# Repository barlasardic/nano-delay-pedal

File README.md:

# Arduino Nano Delay Pedal

A compact guitar delay pedal prototype built around a classic Arduino Nano, with a **300 ms delay target**. The schematic and two-layer PCB are complete as a first hardware draft. **Firmware has not been developed, the circuit has not been built or tested, and the enclosure fit is not confirmed.**

## Revision C layout

The **55.88 × 88.90 mm** PCB has rounded corners and four M2.5 mounting holes. It targets a custom compact pedal enclosure. The [mechanical drawing](docs/mechanical-fit.pdf) shows the proposed enclosure arrangement and an exact PCB mounting template; actual hardware clearances still need confirmation.

Input J2 and output J3 are on opposite side edges. The Nano USB socket faces the right side and overhangs the board by about 1.3 mm. Power traces are wider, the regulator bypass capacitors are closer to U1, and the Nano supply and final ADC filter capacitors sit next to their corresponding Nano pins. The circuit connections and component values are unchanged from revision B.

Component values are printed on the front where space permits. The back includes all 57 reference/value labels, connector functions and polarities. See the [two-page assembly guide](docs/assembly-top.pdf) and [review notes](docs/design-review.md).

## Hardware

- **55.88 × 88.90 mm**, two-layer PCB with four M2.5 mounting holes.
- Socketed Arduino Nano and through-hole components.
- **23LC1024-I/P SPI SRAM** for the planned delay buffer. At 16 ksample/s with 8-bit mono samples, 300 ms requires 4,800 bytes, exceeding the Nano's built-in RAM.
- **MCP6002-I/P** audio buffers on filtered 5 V, with a 2.5 V input bias and approximately 2.7 kHz input/output filter bandwidth.
- **G5V-2-H1 DC5** relay for true bypass; the unpowered/default state is bypass.
- Wired time, feedback and mix pots, audio jacks, momentary footswitch, LED and 9 V power jack.

This is a lo-fi delay design. The external SRAM provides storage; the Nano still performs sampling, delay, mixing, feedback and PWM output. The target delay and audio performance remain to be demonstrated in firmware and bench tests. Board dimensions are intended for a compact pedal; they do not guarantee compatibility with a specific BOSS enclosure.

## Open the project

Open [delay-pedal.kicad_pro](delay-pedal.kicad_pro) in **KiCad 9 or later**. The root schematic and PCB belong to the same revision. The project-local SRAM symbol is included in `Delay.kicad_sym` and `sym-lib-table`; the Nano footprint is in `Delay.pretty` with `fp-lib-table`. Keep both local libraries with the project.

| File / folder | Contents |
|---|---|
| [delay-pedal.kicad_sch](delay-pedal.kicad_sch) | Updated circuit schematic |
| [delay-pedal.kicad_pcb](delay-pedal.kicad_pcb) | Fully routed PCB with ground pours |
| [delay-pedal.pdf](delay-pedal.pdf) | Schematic PDF |
| [Assembly map](docs/assembly-top.pdf) | Top component locations and bottom values/polarities |
| [BOM.txt](BOM.txt) | Manufacturing bill of materials, packages and off-board hardware |
| [Mechanical drawing](docs/mechanical-fit.pdf) | Custom enclosure concept and 1:1 mounting template |
| [Parts list](docs/parts-list.md) | Values, package dimensions and off-board hardware |
| [Hardware and wiring guide](docs/hardware-guide.md) | Pin assignments, assembly, USB power and first checks |
| [Validation reports](docs/checks/) | KiCad ERC, DRC and schematic/PCB agreement results |
| [Prototype manufacturing files](manufacturing/) | Gerbers, plated/non-plated drills, IPC-D-356 netlist, BOM and fabrication notes |

## Power and wiring

Use a **regulated 9 V pedal adapter**. For a center-negative jack, wire its center contact to J1 pin 2 (ground) and its outer contact to J1 pin 1 (+9 V). The jack is mounted off-board.

**Remove the JP1 shunt before connecting USB.** For programming, disconnect 9 V, remove JP1, then connect USB. After programming, disconnect USB, refit JP1 and reconnect 9 V. See the [hardware guide](docs/hardware-guide.md) for the complete procedure and wiring table.

Use three **B10k linear pots** and a **normally-open momentary footswitch**. Verify purchased component dimensions, pinouts and connector polarity against the footprints before assembly. U3 uses MCP6002, not the TL072 from the initial schematic.

## Validation and status

The delivered revision passes KiCad's electrical and PCB design checks with **zero reported violations, zero unconnected pads and zero schematic/PCB agreement issues**. Reports are saved in [docs/checks](docs/checks/). These checks establish CAD consistency; they do not establish functional audio performance.

- [x] Review and revise the schematic
- [x] Add external SRAM and correct input bias and relay protection
- [x] Assign footprints and complete the first PCB layout
- [x] Run KiCad ERC, DRC and schematic/PCB agreement checks
- [x] Export prototype manufacturing files and assembly documentation
- [ ] Confirm supplier part numbers and final enclosure/height clearances
- [ ] Build and power-check a prototype
- [ ] Develop and validate the Arduino firmware
- [ ] Measure delay range, noise, clipping and feedback behavior
- [ ] Test relay switching and revise the hardware as needed

The manufacturing exports are for this **unvalidated prototype**, not a tested production release. Validate the circuit and mechanical fit before ordering a production batch. Older schematic revisions are retained in Git history.

## License

See [LICENSE](LICENSE).

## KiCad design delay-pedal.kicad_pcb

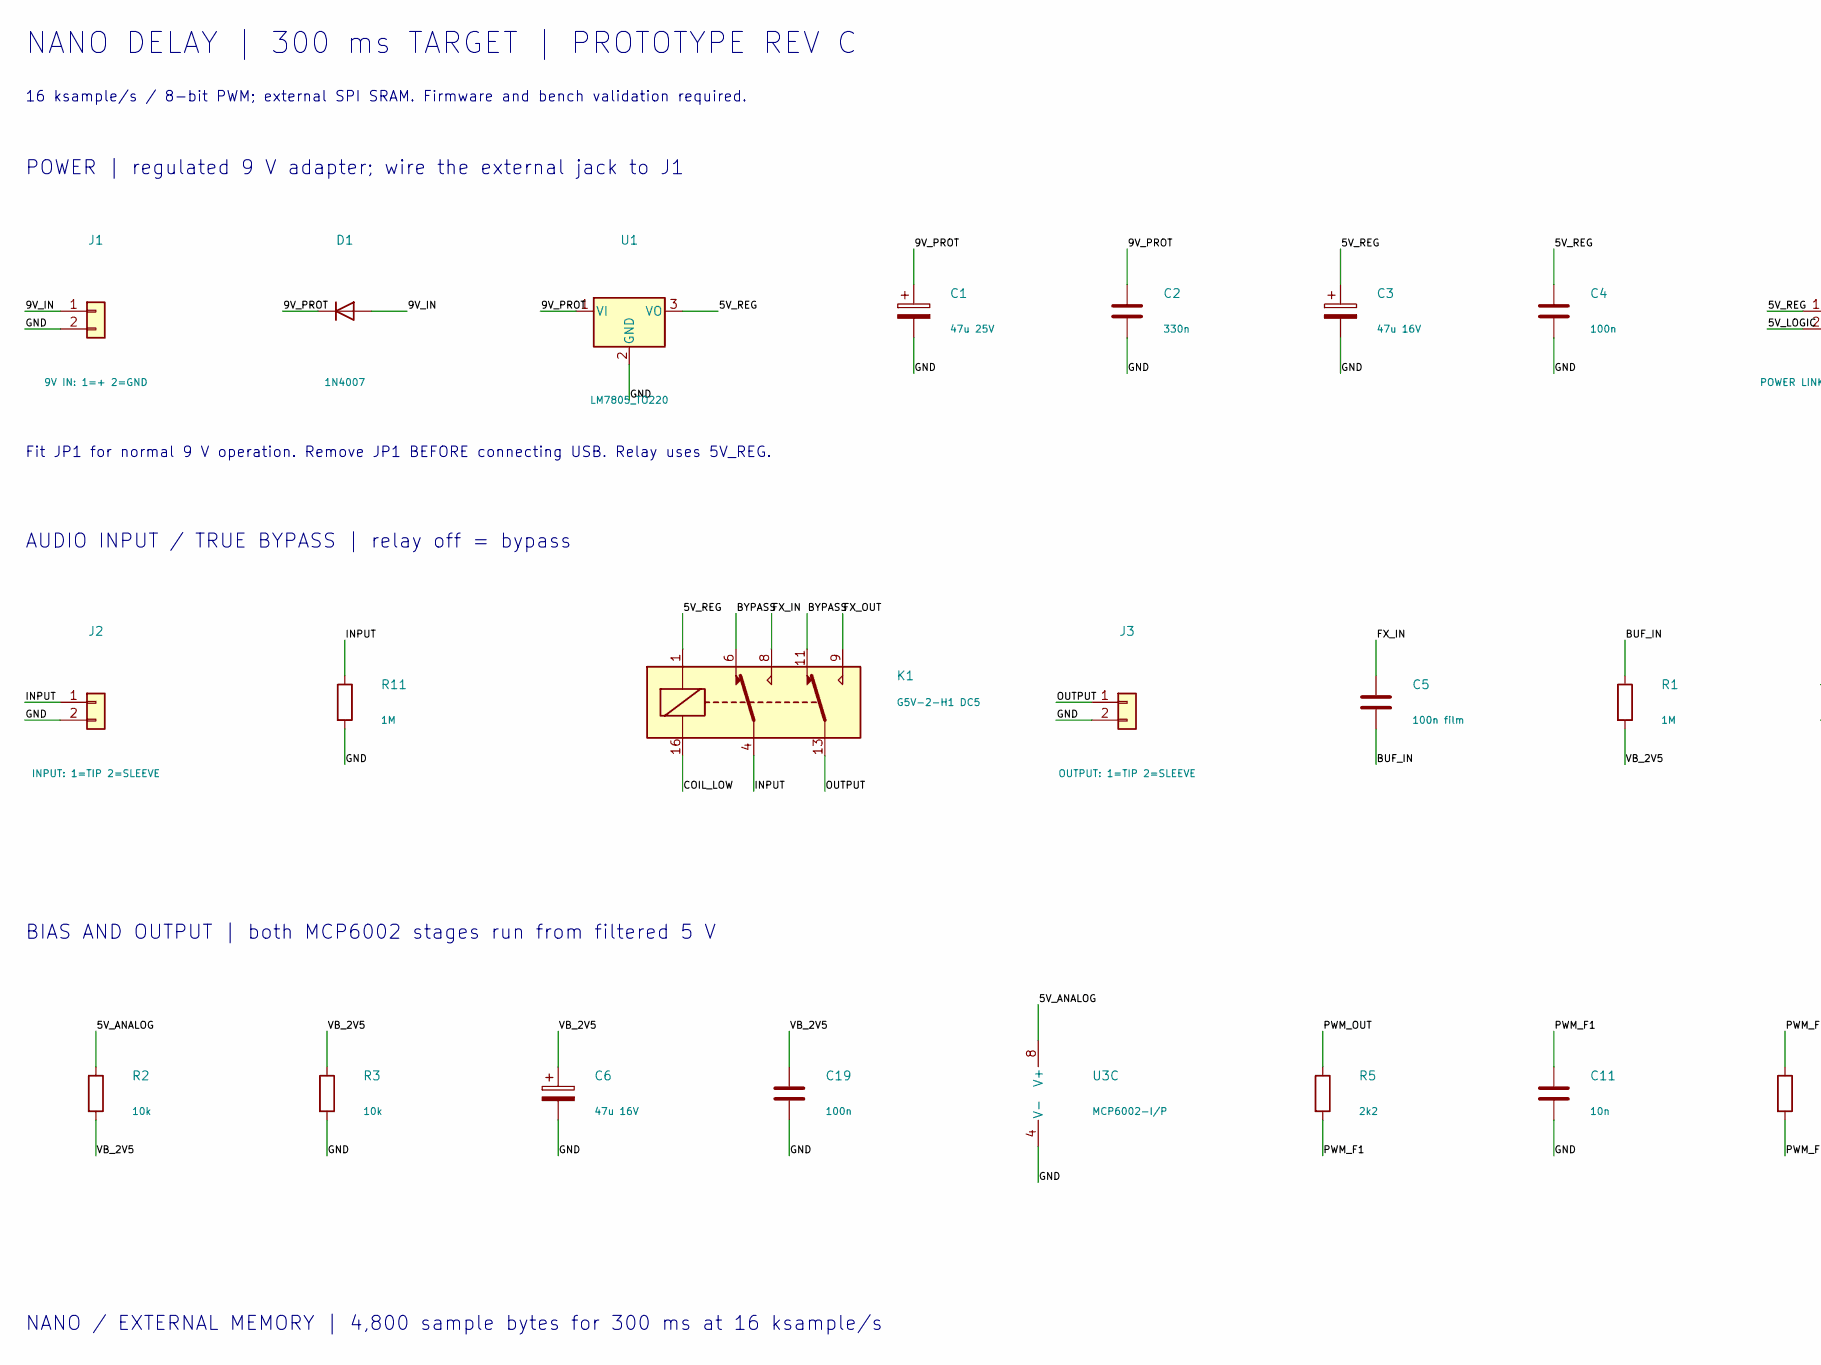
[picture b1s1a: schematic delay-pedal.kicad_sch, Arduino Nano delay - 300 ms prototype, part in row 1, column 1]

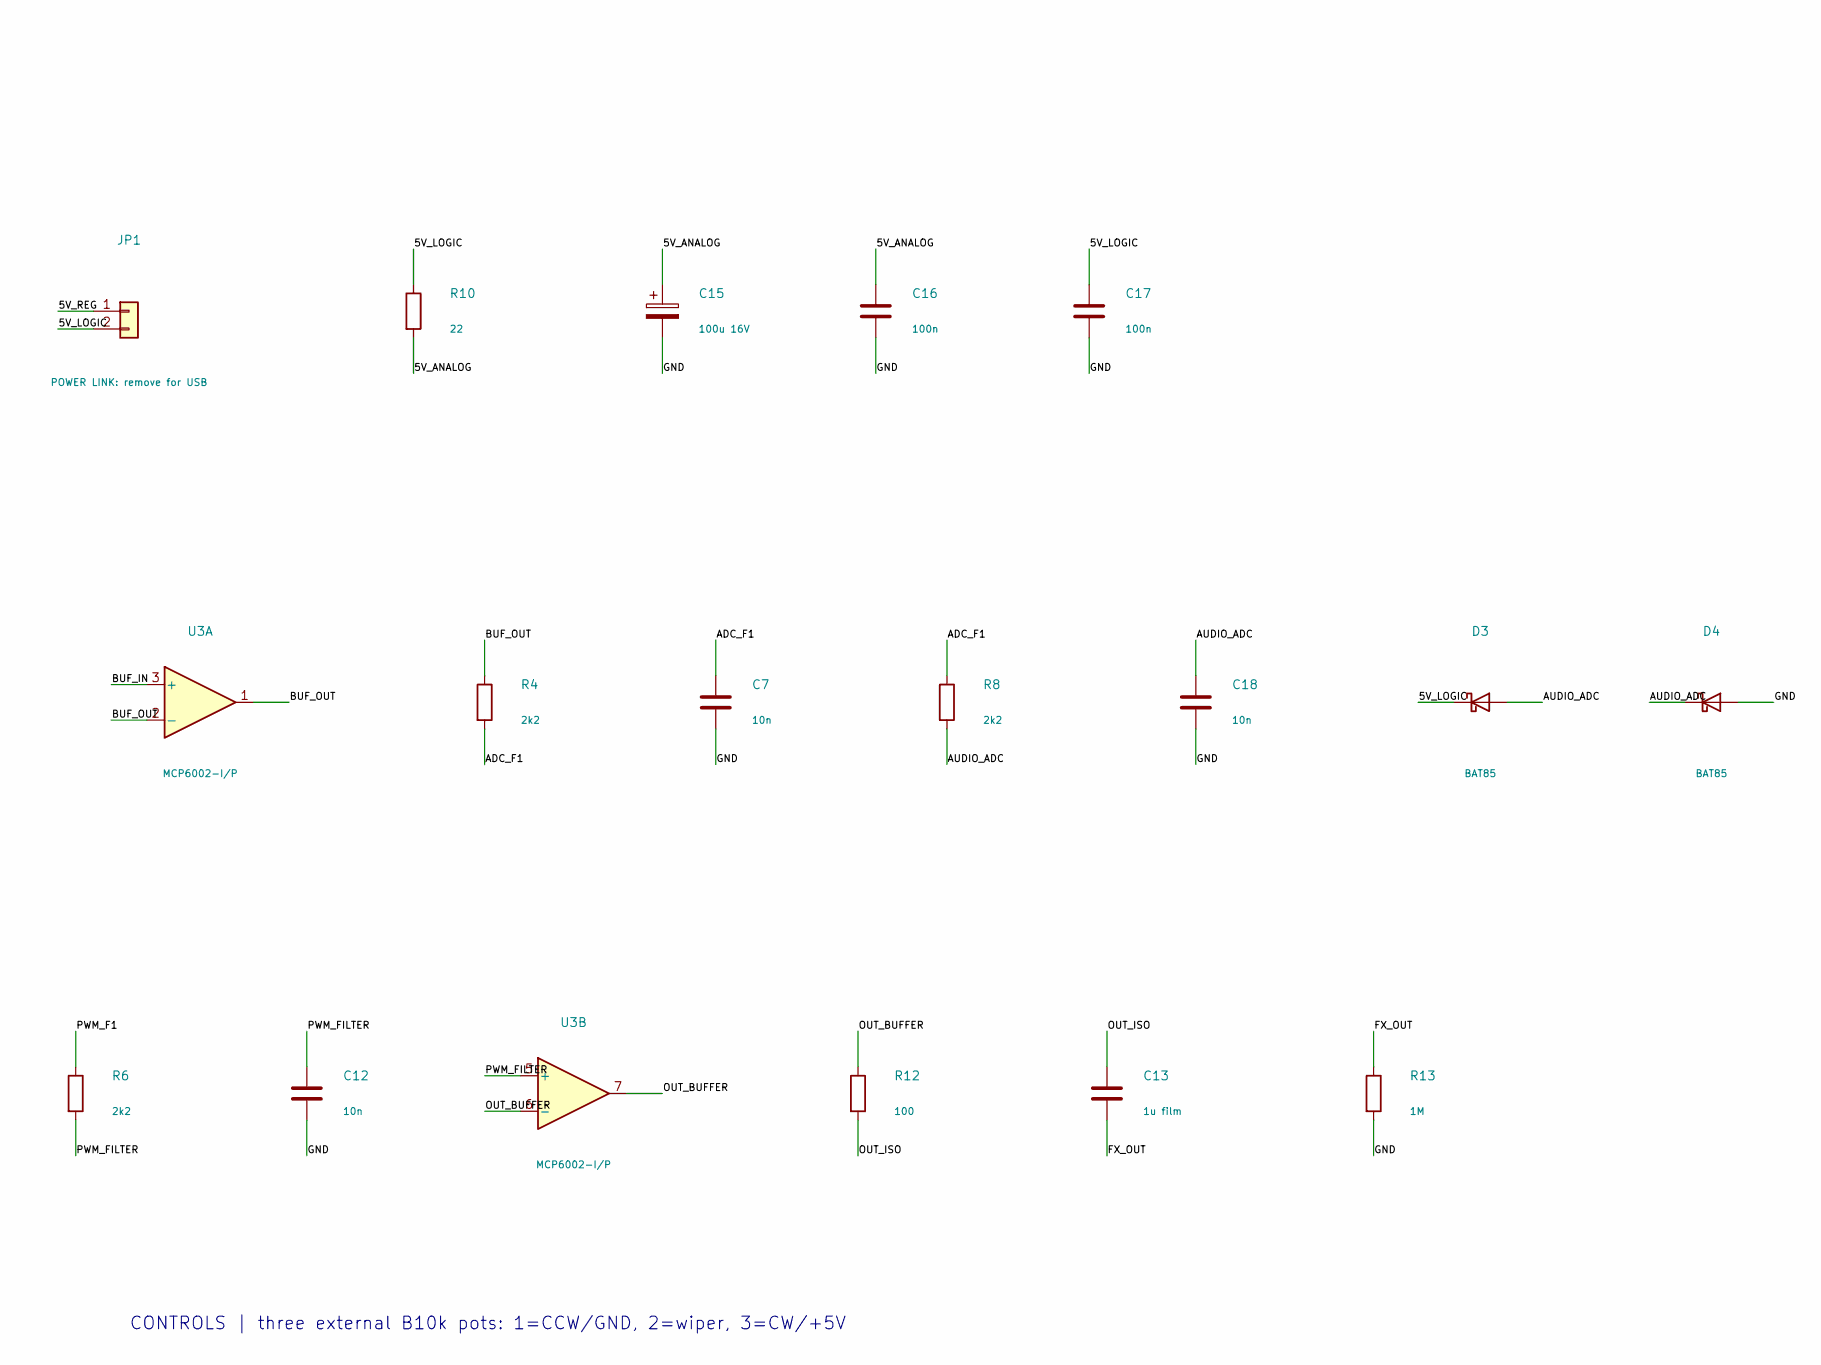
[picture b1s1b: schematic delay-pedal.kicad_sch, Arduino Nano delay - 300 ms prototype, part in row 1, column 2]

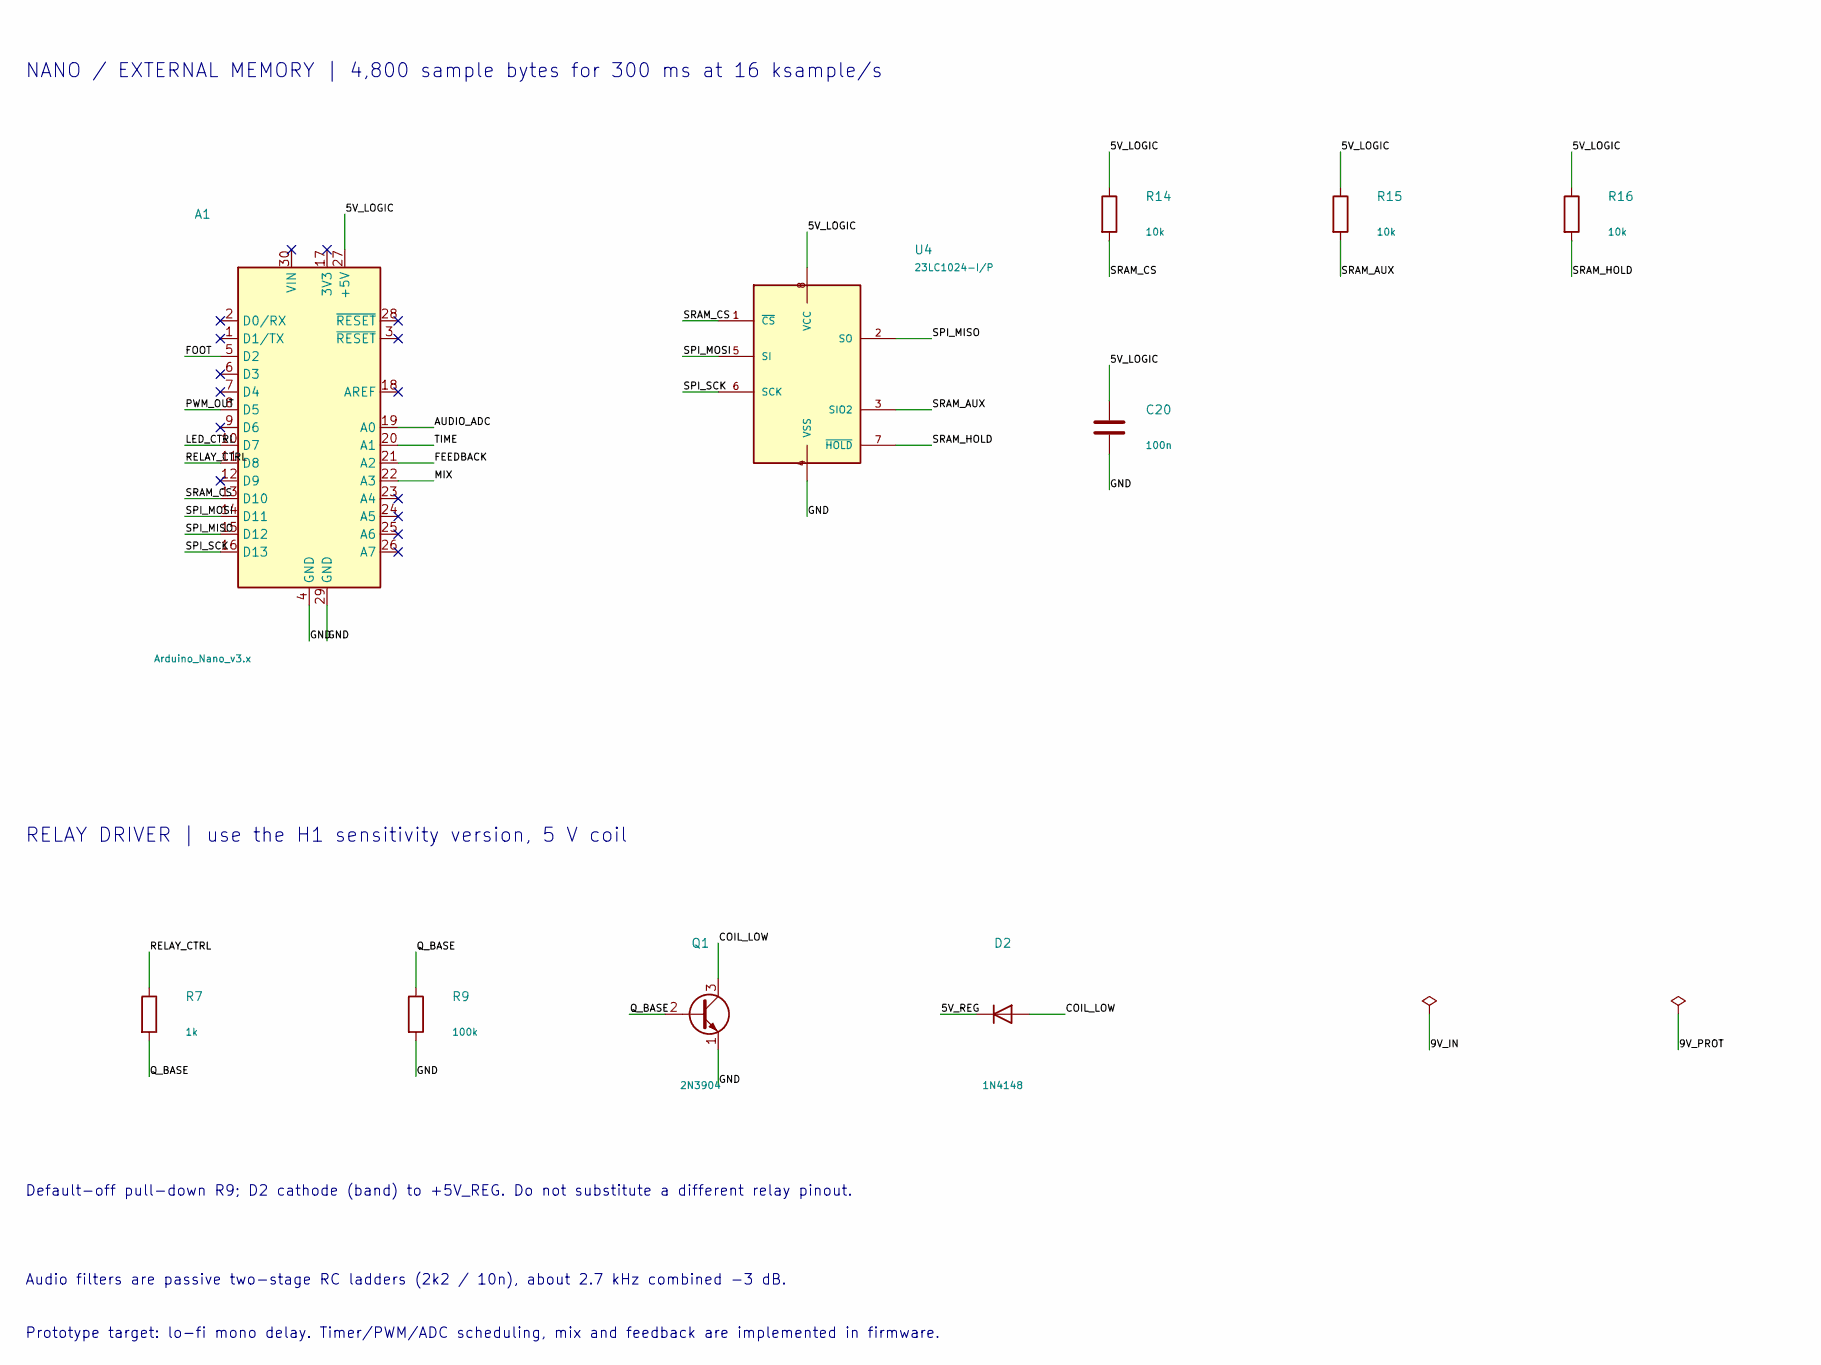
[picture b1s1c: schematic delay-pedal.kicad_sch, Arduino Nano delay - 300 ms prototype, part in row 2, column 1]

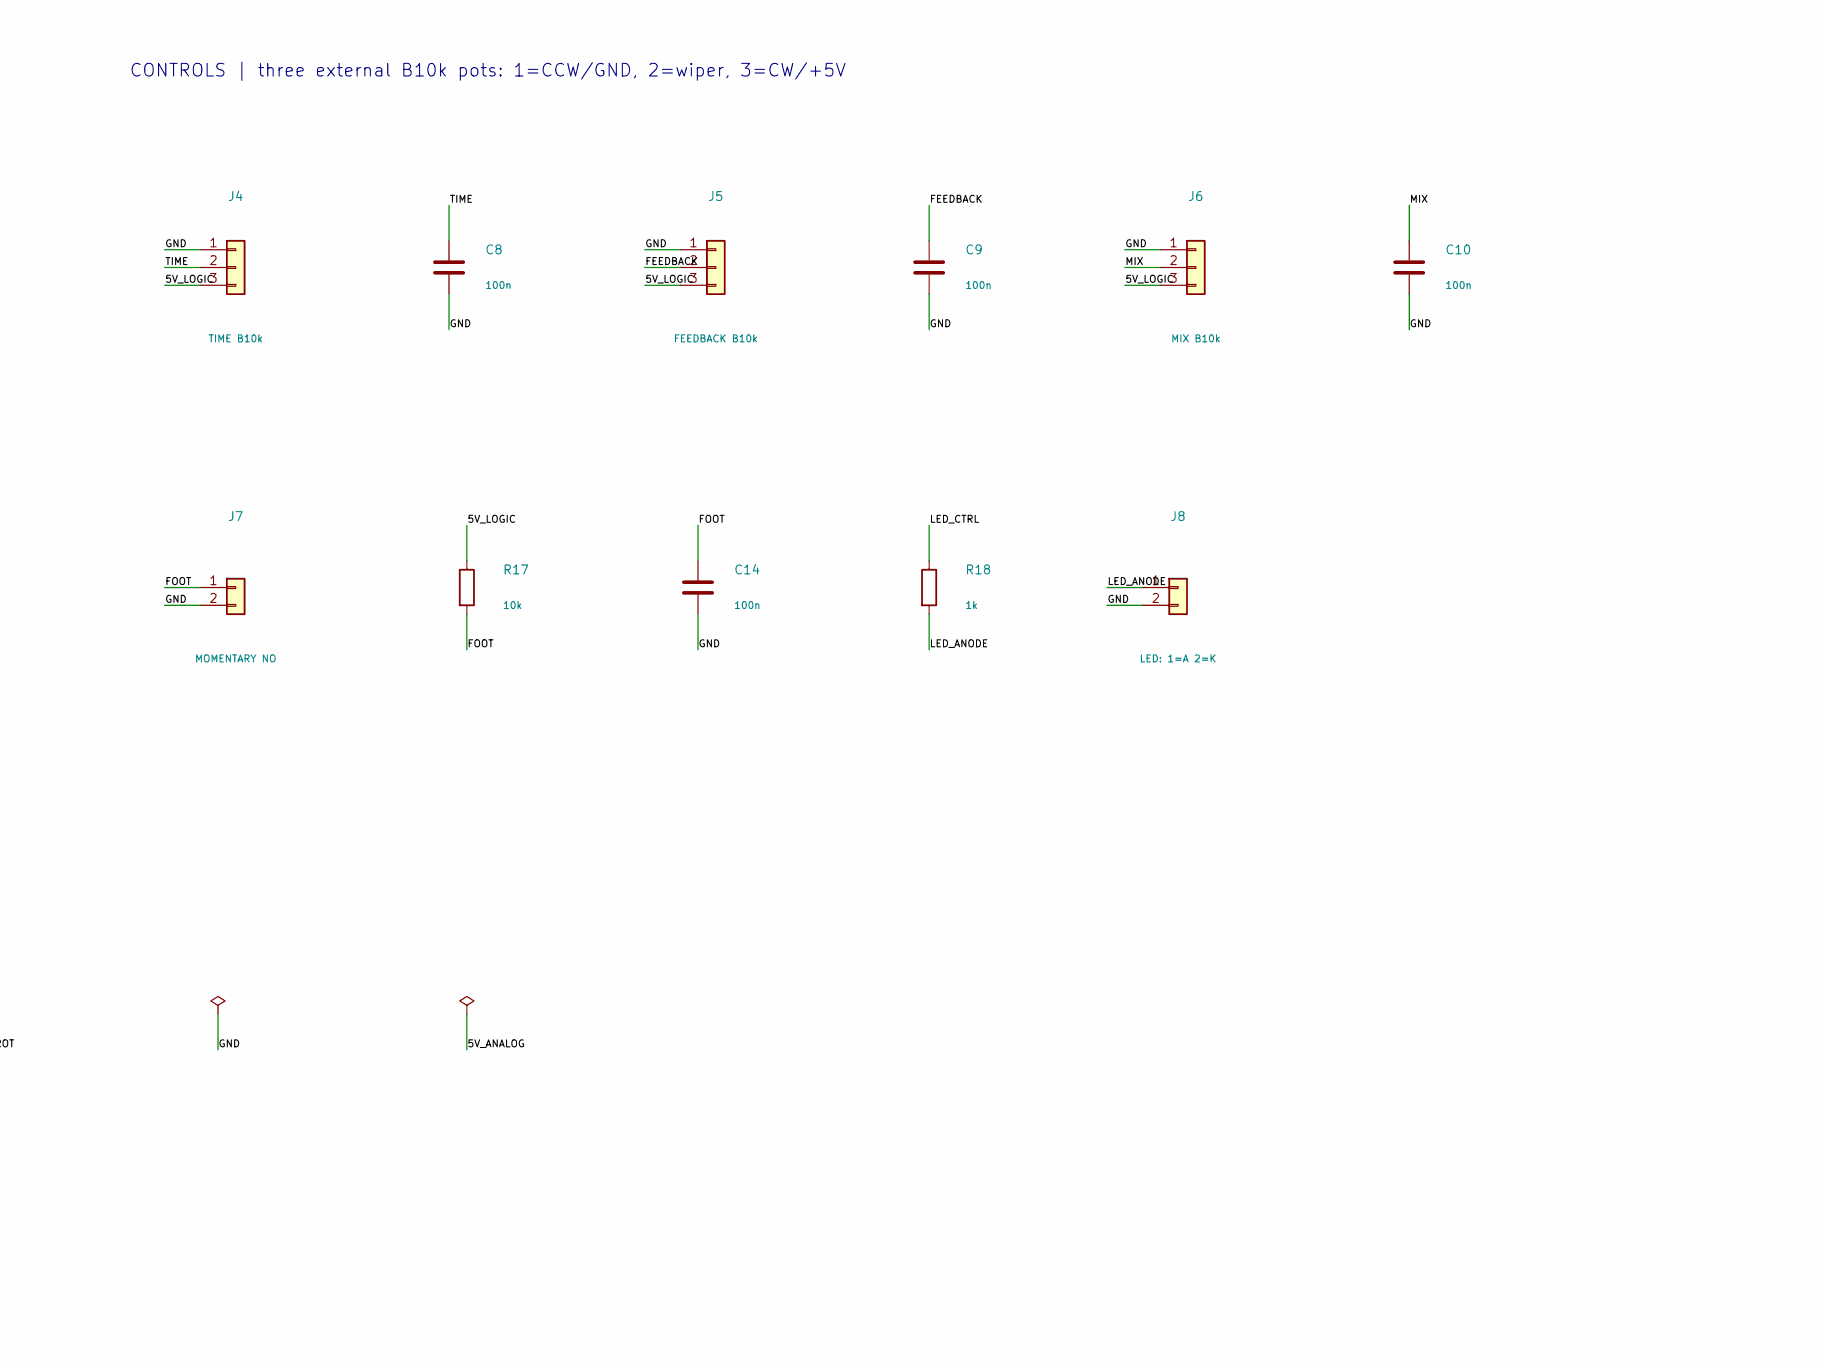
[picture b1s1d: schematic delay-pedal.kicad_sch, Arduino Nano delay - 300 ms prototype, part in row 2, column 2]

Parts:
A1: Arduino_Nano_v3.x; Arduino_Nano_EdgeUSB
C1: 47u 25V; CP_Radial_D6.3mm_P2.50mm
C2: 330n; C_Disc_D3.0mm_W1.6mm_P2.50mm
C3, C6: 47u 16V; CP_Radial_D6.3mm_P2.50mm
C4, C8, C9, C10, C14, C16, C17, C19, C20: 100n; C_Disc_D3.0mm_W1.6mm_P2.50mm
C5: 100n film; C_Rect_L7.2mm_W2.5mm_P5.00mm
C7, C11, C12, C18: 10n; C_Disc_D3.0mm_W1.6mm_P2.50mm
C13: 1u film; C_Rect_L7.2mm_W3.5mm_P5.00mm
C15: 100u 16V; CP_Radial_D6.3mm_P2.50mm
D1: 1N4007; D_DO-41_SOD81_P10.16mm_Horizontal
D2: 1N4148; D_DO-35_SOD27_P7.62mm_Horizontal
D3, D4: BAT85; D_DO-35_SOD27_P7.62mm_Horizontal
J1: 9V IN: 1=+ 2=GND; PinHeader_1x02_P2.54mm_Vertical
J2: INPUT: 1=TIP 2=SLEEVE; PinHeader_1x02_P2.54mm_Vertical
J3: OUTPUT: 1=TIP 2=SLEEVE; PinHeader_1x02_P2.54mm_Vertical
J4: TIME B10k; PinHeader_1x03_P2.54mm_Vertical
J5: FEEDBACK B10k; PinHeader_1x03_P2.54mm_Vertical
J6: MIX B10k; PinHeader_1x03_P2.54mm_Vertical
J7: MOMENTARY NO; PinHeader_1x02_P2.54mm_Vertical
J8: LED: 1=A 2=K; PinHeader_1x02_P2.54mm_Vertical
JP1: POWER LINK: remove for USB; PinHeader_1x02_P2.54mm_Vertical
K1: G5V-2-H1 DC5; Relay_DPDT_Omron_G5V-2
Q1: 2N3904; TO-92_Inline_Wide
R1, R11, R13: 1M; R_Axial_DIN0204_L3.6mm_D1.6mm_P7.62mm_Horizontal
R2, R3, R14, R15, R16, R17: 10k; R_Axial_DIN0204_L3.6mm_D1.6mm_P7.62mm_Horizontal
R4, R5, R6, R8: 2k2; R_Axial_DIN0204_L3.6mm_D1.6mm_P7.62mm_Horizontal
R7, R18: 1k; R_Axial_DIN0204_L3.6mm_D1.6mm_P7.62mm_Horizontal
R9: 100k; R_Axial_DIN0204_L3.6mm_D1.6mm_P7.62mm_Horizontal
R10: 22; R_Axial_DIN0204_L3.6mm_D1.6mm_P7.62mm_Horizontal
R12: 100; R_Axial_DIN0204_L3.6mm_D1.6mm_P7.62mm_Horizontal
U1: LM7805_TO220; TO-220-3_Vertical
U3: MCP6002-I/P; DIP-8_W7.62mm_Socket
U4: 23LC1024-I/P; DIP-8_W7.62mm_Socket

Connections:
/5V_ANALOG: C15.1, C16.1, R2.1, R10.2, U3.8 (V+)
/5V_LOGIC: A1.27 (+5V), C17.1, C20.1, D3.1 (K), J4.3, J5.3, J6.3, JP1.2, R10.1, R14.1, R15.1, R16.1, R17.1, U4.8 (VCC)
/5V_REG: C3.1, C4.1, D2.1 (K), JP1.1, K1.1, U1.3 (VO)
/9V_IN: D1.2 (A), J1.1
/9V_PROT: C1.1, C2.1, D1.1 (K), U1.1 (VI)
/ADC_F1: C7.1, R4.2, R8.1
/AUDIO_ADC: A1.19 (A0), C18.1, D3.2 (A), D4.1 (K), R8.2
/BUF_IN: C5.2, R1.1, U3.3 (+)
/BUF_OUT: R4.1, U3.1, U3.2 (-)
/BYPASS: K1.6, K1.11
/COIL_LOW: D2.2 (A), K1.16, Q1.3 (C)
/FEEDBACK: A1.21 (A2), C9.1, J5.2
/FOOT: A1.5 (D2), C14.1, J7.1, R17.2
/FX_IN: C5.1, K1.8
/FX_OUT: C13.2, K1.9, R13.1
/GND: A1.4 (GND), A1.29 (GND), C1.2, C2.2, C3.2, C4.2, C6.2, C7.2, C8.2, C9.2, C10.2, C11.2, C12.2, C14.2, C15.2, C16.2, C17.2, C18.2, C19.2, C20.2, D4.2 (A), J1.2, J2.2, J3.2, J4.1, J5.1, J6.1, J7.2, J8.2, Q1.1 (E), R3.2, R9.2, R11.2, R13.2, U1.2 (GND), U3.4 (V-), U4.4 (VSS)
/INPUT: J2.1, K1.4, R11.1
/LED_ANODE: J8.1, R18.2
/LED_CTRL: A1.10 (D7), R18.1
/MIX: A1.22 (A3), C10.1, J6.2
/OUTPUT: J3.1, K1.13
/OUT_BUFFER: R12.1, U3.6 (-), U3.7
/OUT_ISO: C13.1, R12.2
/PWM_F1: C11.1, R5.2, R6.1
/PWM_FILTER: C12.1, R6.2, U3.5 (+)
/PWM_OUT: A1.8 (D5), R5.1
/Q_BASE: Q1.2 (B), R7.2, R9.1
/RELAY_CTRL: A1.11 (D8), R7.1
/SPI_MISO: A1.15 (D12), U4.2 (SO)
/SPI_MOSI: A1.14 (D11), U4.5 (SI)
/SPI_SCK: A1.16 (D13), U4.6 (SCK)
/SRAM_AUX: R15.2, U4.3 (SIO2)
/SRAM_CS: A1.13 (D10), R14.2, U4.1 (~CS)
/SRAM_HOLD: R16.2, U4.7 (~HOLD)
/TIME: A1.20 (A1), C8.1, J4.2
/VB_2V5: C6.1, C19.1, R1.2, R2.2, R3.1

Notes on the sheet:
NANO DELAY | 300 ms TARGET | PROTOTYPE REV C
16 ksample/s / 8-bit PWM; external SPI SRAM. Firmware and bench validation required.
POWER | regulated 9 V adapter; wire the external jack to J1
Fit JP1 for normal 9 V operation. Remove JP1 BEFORE connecting USB. Relay uses 5V_REG.
AUDIO INPUT / TRUE BYPASS | relay off = bypass
BIAS AND OUTPUT | both MCP6002 stages run from filtered 5 V
NANO / EXTERNAL MEMORY | 4,800 sample bytes for 300 ms at 16 ksample/s
CONTROLS | three external B10k pots: 1=CCW/GND, 2=wiper, 3=CW/+5V
RELAY DRIVER | use the H1 sensitivity version, 5 V coil
Default-off pull-down R9; D2 cathode (band) to +5V_REG. Do not substitute a different relay pinout.
Audio filters are passive two-stage RC ladders (2k2 / 10n), about 2.7 kHz combined -3 dB.
Prototype target: lo-fi mono delay. Timer/PWM/ADC scheduling, mix and feedback are implemented in firmware.

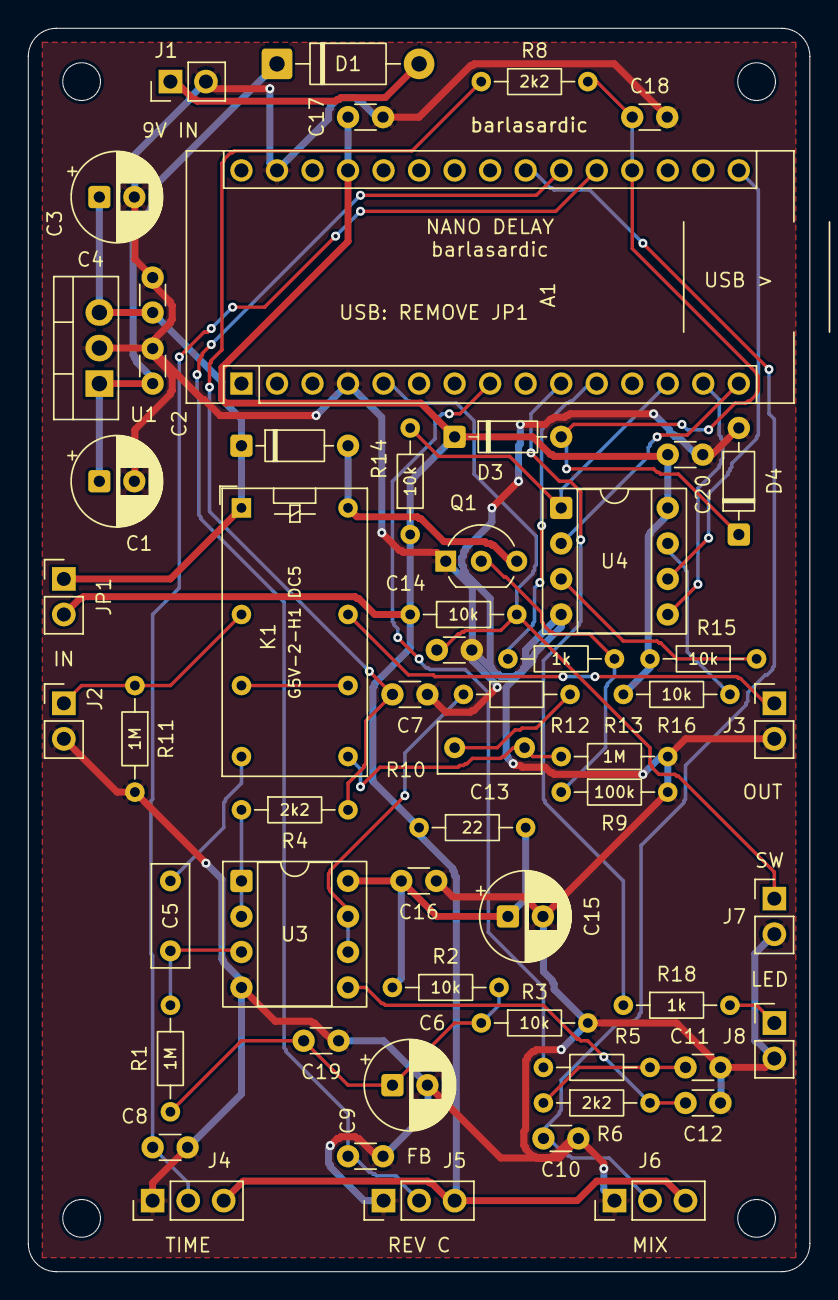
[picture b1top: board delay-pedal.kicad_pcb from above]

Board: 2 copper layers, 55.9 x 88.9 mm, 61 parts (0 on the bottom side), 36 nets.

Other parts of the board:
H1, H2, H3, H4: M2.5; MountingHole_2.7mm_M2.5

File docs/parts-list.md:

# Parts list — prototype revision C

See [BOM.txt](../BOM.txt) for the plain-text manufacturing BOM.

Select parts by both electrical value and the footprint dimensions. Resistors use compact DIN0204 bodies (about 3.6 × 1.6 mm), 7.62 mm lead spacing, 1% tolerance, at least 0.125 W. Standard larger quarter-watt bodies may need a footprint/layout change.

| References | Qty | Value / part | Package |
|---|---:|---|---|
| A1 | 1 | Arduino_Nano_v3.x | Arduino_Nano_EdgeUSB (project-local Delay library) |
| C1 | 1 | 47u 25V | CP_Radial_D6.3mm_P2.50mm |
| C2 | 1 | 330n | C_Disc_D3.0mm_W1.6mm_P2.50mm |
| C3, C6 | 2 | 47u 16V | CP_Radial_D6.3mm_P2.50mm |
| C4, C8, C9, C10, C14, C16, C17, C19, C20 | 9 | 100n | C_Disc_D3.0mm_W1.6mm_P2.50mm |
| C5 | 1 | 100n film | C_Rect_L7.2mm_W2.5mm_P5.00mm |
| C7, C11, C12, C18 | 4 | 10n | C_Disc_D3.0mm_W1.6mm_P2.50mm |
| C13 | 1 | 1u film | C_Rect_L7.2mm_W3.5mm_P5.00mm |
| C15 | 1 | 100u 16V | CP_Radial_D6.3mm_P2.50mm |
| D1 | 1 | 1N4007 | D_DO-41_SOD81_P10.16mm_Horizontal |
| D2 | 1 | 1N4148 | D_DO-35_SOD27_P7.62mm_Horizontal |
| D3, D4 | 2 | BAT85 | D_DO-35_SOD27_P7.62mm_Horizontal |
| J1 | 1 | 9V IN: 1=+ 2=GND | PinHeader_1x02_P2.54mm_Vertical |
| J2 | 1 | INPUT: 1=TIP 2=SLEEVE | PinHeader_1x02_P2.54mm_Vertical |
| J3 | 1 | OUTPUT: 1=TIP 2=SLEEVE | PinHeader_1x02_P2.54mm_Vertical |
| J4 | 1 | TIME B10k | PinHeader_1x03_P2.54mm_Vertical |
| J5 | 1 | FEEDBACK B10k | PinHeader_1x03_P2.54mm_Vertical |
| J6 | 1 | MIX B10k | PinHeader_1x03_P2.54mm_Vertical |
| J7 | 1 | MOMENTARY NO | PinHeader_1x02_P2.54mm_Vertical |
| J8 | 1 | LED: 1=A 2=K | PinHeader_1x02_P2.54mm_Vertical |
| JP1 | 1 | POWER LINK: remove for USB | PinHeader_1x02_P2.54mm_Vertical |
| K1 | 1 | G5V-2-H1 DC5 | Relay_DPDT_Omron_G5V-2 |
| Q1 | 1 | 2N3904 | TO-92_Inline_Wide |
| R1, R11, R13 | 3 | 1M | R_Axial_DIN0204_L3.6mm_D1.6mm_P7.62mm_Horizontal |
| R2, R3, R14, R15, R16, R17 | 6 | 10k | R_Axial_DIN0204_L3.6mm_D1.6mm_P7.62mm_Horizontal |
| R4, R5, R6, R8 | 4 | 2k2 | R_Axial_DIN0204_L3.6mm_D1.6mm_P7.62mm_Horizontal |
| R7, R18 | 2 | 1k | R_Axial_DIN0204_L3.6mm_D1.6mm_P7.62mm_Horizontal |
| R9 | 1 | 100k | R_Axial_DIN0204_L3.6mm_D1.6mm_P7.62mm_Horizontal |
| R10 | 1 | 22 | R_Axial_DIN0204_L3.6mm_D1.6mm_P7.62mm_Horizontal |
| R12 | 1 | 100 | R_Axial_DIN0204_L3.6mm_D1.6mm_P7.62mm_Horizontal |
| U1 | 1 | LM7805_TO220 | TO-220-3_Vertical |
| U3 | 1 | MCP6002-I/P | DIP-8_W7.62mm_Socket |
| U4 | 1 | 23LC1024-I/P | DIP-8_W7.62mm_Socket |

## Extra hardware

- Two 1×15 female sockets, 2.54 mm pitch, for the Nano.
- Two DIP-8 sockets with 7.62 mm row spacing, if not already counted with IC purchases.
- Three B10k linear pots, knobs and mounting hardware.
- Two mono 6.35 mm panel jacks.
- One insulated panel DC jack compatible with the chosen regulated 9 V center-negative adapter.
- One normally-open momentary footswitch.
- One LED; its series 1 kΩ resistor is already R18 on the PCB.
- One 2.54 mm shunt for JP1.
- Four M2.5 insulating standoffs and screws; verify actual head/washer clearance.
- Hookup wire, short shielded audio cable, and secure header plugs if desired.

Capacitor packages: 100 nF/10 nF small ceramics use a 2.50 mm pitch and 3 mm disc body. Electrolytics use 2.50 mm pitch, 6.3 mm diameter; verify height. C5 uses a 7.2 × 2.5 mm, 5 mm pitch film body. C13 uses a 7.2 × 3.5 mm, 5 mm pitch film body; select a 1 µF part that fits (typically a compact 50 V polyester part). Do not substitute a wider film capacitor without checking neighboring parts.

The exact purchasing BOM remains to be confirmed against available supplier part numbers. Values and package envelopes are specified here; this is not a supplier-validated cart.
